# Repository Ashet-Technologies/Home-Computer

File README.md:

# Ashet Home Computer Mk4

### _The 21st century home computer_

| Project Status                                                                                       |
|------------------------------------------------------------------------------------------------------|
| ⚠️ **WORK IN PROGRESS** ⚠️                                                                             |
| This README reflects the state of where the project wants to go, not where the project is right now! |

## Introduction

The Ashet Home Computer bridges the gap between simple microcontroller development boards and modern single-board computers, offering the processing capability to run a full graphical desktop OS while maintaining the hardware accessibility of simpler systems.

Built around the RP2350 dual-core processor, it combines sufficient computational power for a modern user interface with a transparent, education-oriented architecture. The modular expansion system, inspired by classic computer designs, allows direct hardware access while providing proper driver abstractions for portability.

Key differentiators:

- Runs [Ashet OS](https://github.com/Ashet-Technologies/Ashet-OS): A custom desktop operating system with modern GUI capabilities
- Fully documented hardware architecture with direct register access
- Modular expansion through 7 dedicated slots, including specialized video/audio interfaces
- 8 MB RAM and 16 MB Flash supporting both low-level and high-level development
- Comprehensive I/O capabilities suitable for real-time interfacing, creative projects, and systems development

The system is designed for accessibility across different skill levels - from students learning computer architecture to makers building custom hardware interfaces, and from demosceners pushing hardware limits to educators teaching system design.

## Features

The computer follows a modular design similar to a PC where you have expansion cards that you can plug into the system.

### Core Features

These features are available no matter what expansion cards you have installed.

- RP2350 Core
  - Dual-Core System
  - Each Core Might Be
    - Arm CPU (Cortex-M33, 150 MHz)
    - RISC-V CPU (RV32IMAC+, 150 MHz)
- 8 MB RAM
- 16 MB Flash
- USB 1.1 Host
- 10/100 Mbps Ethernet
- Battery-Backed Real-Time Clock
- Status Display (128x64, monochrome)
- Integrated Debug Probe
- 7 Expansion Slots
  - 1 Video Expansion Slot
  - 1 Audio Expansion Slot
  - 5 Generic Expansion Slots

### Standard Expansions

The following expansion cards are the designated expansion cards which make up the Ashet Home Computer as designed:

1. [Framebuffer Video Card](Hardware/Expansions/Framebuffer%20Video/README.md)
    - DVI Video Out (800x480, 60 Hz)
2. [PCM Sound Card](Hardware/Expansions/PCM%20Sound/README.md)
    - PCM Audio Out (48 kHz, 16 bit)
    - PCM Audio In (48 kHz, 16 bit)
3. [USB Card](Hardware/Expansions/USB/README.md)
    - 4 USB 1.1 Host Ports
4. [RS232 Card](Hardware/Expansions/RS232/README.md)
    - TTL UART (3.3V, 5V, ±12V)
5. [Basic I/O Card](Hardware/Expansions/Basic%20IO/README.md)
    - Pin Header Connector
    - 8 GPIOs
    - Dedicated I²C
    - 5 V and 3.3 V power supply available
6. [Commodore Connectivity Card](Hardware/Expansions/Commodore%20Connectivity/README.md)
    - 2× C64 Serial
7. [User Expansion Card](Hardware/Expansions/User%20Expansion/README.md)
    - Minimal Expansion Card
    - Perfboard For Custom Expansions
    - Pin Header Connector

### Other Expansions

There are many more ideas that can be realized with expansion cards.

Take a peek at our [List of Expansion Board Ideas](Concept/Expansion%20Boards.md) or check out the [Expansion Card Interface Specification](Specs/Expansion%20Bus.md) how to create your own.

## Use Cases

This chapter contains a list of things you can do with the computer, ordered loosely by user groups.

### Demosceners

Make a demo, I guess?

With a good audio and video expansion card, and two strong multi-core CPUs the computer packs enough power to create awesome visuals and sound effects.

### Retro-Enthusiasts

The computer is able to emulate a lot of existing machines with fitting I/O connectivity. The backplane is able to emulate a lot of different protocols with cheap passive expansion modules.

It also is able to create a multitude of video signals, analog and digital with 15 or 30 kHz line frequency. Another option is to have more complex expansion cards which can drive storage interfaces like [Shugart bus](https://en.wikipedia.org/wiki/Floppy_disk_drive_interface), [MFM disks](https://en.wikipedia.org/wiki/Modified_frequency_modulation), ATA and IDE…

### Artists / Musicians

The Ashet can be used as a cheap real-time sequencing controller which can handle a good amount of interfaces. With support for MIDI, DMX, analog audio channels and ethernet, it's possible to create complex audio setups. Another option is creating or using expansion cards that provide access to old-school synthesizers like the [AY-3-8910](https://en.wikipedia.org/wiki/General_Instrument_AY-3-8910) or the [SID](https://en.wikipedia.org/wiki/MOS_Technology_6581).

### Hackers / Makers

With the Propeller 2 on the backplane, one can basically emulate any digital interface like SPI or I²C. With a breakout I/O expansion card, it can be used for controlling your own hardware, accessing and changing SPI flashes, ...

It is also possible to use the Ashet as a basic logic analyzer and scope, as well as a signal and waveform generator. With a bigger I/O card, it can be expanded to 32 synchronously processed channels.

By utilizing a scripting language on Ashet OS, one should be able to easily access and bootstrap newly acquired hardware.

### Educators

The project provides extensive documentation, from decision making over the schematic up to the software architecture, so it can be used as an example on how to design a complete computer system.

The machine also looks more like a "real computer" than a Raspberry Pi or other modern single-board computers, so it is more tangible for persons that do not have experience with electronics and might give an easier start.

### Students

The computer provides a good hands-on experience and allows both creating or understanding hardware and software designs and how they play together. The system is also easily expansible and thus allows creating custom hardware modules. The available documentation allows learning basically everything about the computer that is possible to know.

## Comparison with Similar Projects

The following table shows a comparison to other "small" computers. It should help you get an idea where the Ashet Home Computer is in relation to other projects.

| Feature                      | Ashet                                                              | [Raspberry Pi 4](https://www.raspberrypi.com/products/raspberry-pi-4-model-b/specifications/)   | [Arduino Uno REV3](https://store.arduino.cc/products/arduino-uno-rev3) | [Neotron Pico](https://github.com/neotron-Compute/neotron-Pico)                                                                   | [Cody Computer](https://www.codycomputer.org/)          |
|------------------------------|--------------------------------------------------------------------|-------------------------------------------------------------------------------------------------|------------------------------------------------------------------------|-----------------------------------------------------------------------------------------------------------------------------------|---------------------------------------------------------|
| CPU Architecture             | Arm Cortex-M33 (32 bit)                                            | Arm Cortex-A72 (64 bit)                                                                         | ATmega328p (8 bit)                                                     | Arm Cortex-M0+ (32 bit)                                                                                                           | 6502                                                    |
| CPU Model                    | [Rapsberry Pi RP2350](https://www.raspberrypi.com/products/rp2350/) | [Broadcom BCM2711](https://www.raspberrypi.com/documentation/computers/processors.html#bcm2711) | [ATmega328P](https://www.microchip.com/en-us/product/atmega328p)       | [Rapsberry Pi RP2040](https://www.raspberrypi.com/products/rp2040/)                                                               | [W65C02S](https://wdc65xx.com/integrated-circuit)       |
| CPU Cores                    | 2                                                                  | 4                                                                                               | 1                                                                      | 2                                                                                                                                 | 1                                                       |
| CPU Clock                    | 150 MHz                                                            | 1.8 GHz                                                                                         | 16 MHz                                                                 | 133 MHz                                                                                                                           | 1 MHz                                                   |
| System Memory                | 8 MB                                                               | 1, 2, 4 or 8 GB                                                                                 | 2 KB                                                                   | 264 kB                                                                                                                            | 64 kB                                                   |
| Understandable               | ✅                                                                  | ❌                                                                                               | ✅                                                                      | ✅                                                                                                                                 | ✅                                                       |
| Modern I/O                   | ✅                                                                  | ✅                                                                                               | ❌                                                                      | ❌¹                                                                                                                                | ❌                                                       |
| Modular Design               | ✅                                                                  | ❌                                                                                               | ❌                                                                      | ✅                                                                                                                                 | ✅²                                                      |
| Full Documentation Available | ✅                                                                  | ❌                                                                                               | ✅                                                                      | ✅                                                                                                                                 | ✅                                                       |
| Ethernet                     | ✅                                                                  | ✅                                                                                               | ❌                                                                      | ❌                                                                                                                                 | ❌                                                       |
| Parallax Propeller I/O Chip  | ✅ ([Propeller 2](https://www.parallax.com/propeller-2))            | ❌                                                                                               | ❌                                                                      | ❌                                                                                                                                 | ✅ ([Propeller 1](https://www.parallax.com/propeller-1)) |

¹Neotron Pico uses PS/2 for mouse/keyboard and VGA for video.

²Cody Computer has a single cartridge that can be added.

## Architecture

### Block Diagram

## Glossary

<dl>
  <dt>Mainboard</dt>
  <dd>The Mainboard houses the cpu core and everything necessary to run the system, even without <em>Expansion Boards</em> or the <em>Backplane</em>.</dd>

  <dt>Backplane</dt>
  <dd>The Backplane is the interconnect between the <em>Mainboard</em> and <em>Expansion Boards</em>. This board also contains the <em>I/O Southbridge</em></dd>

  <dt>Expansion Board</dt>
  <dd>Expansion Boards provide more capabilities to the computer. They usually add more I/O features, but could also house any other kind of electronics that want to interface with the <em>Mainboard</em>.</dd>

  <dt>Video Expansion Board</dt>
  <dd>A Video Expansion Board is a special expansion that is only installable in a single socket of the <em>Backplane</em>. In addition to the generic <em>Expansion Board</em> interface, it has an additional 8 lanes of high-speed interconnect to the <em>Mainboard</em>.</dd>

  <dt>Audio Expansion</dt>
  <dd>An Audio Expansion Board is a special expansion that is only installable in a single socket of the <em>Backplane</em>. In addition to the generic <em>Expansion Board</em> interface, it has an additional 2-lane I²S interconnect to the <em>Mainboard</em>.</dd>

  <dt>I/O Southbridge</dt>
  <dd>The I/O Southbridge provides the main interconnect between the <em>Main Board</em> and the <em>Expansion Boards</em>. It is realized by a <a href="https://www.parallax.com/propeller-2/">Propeller 2</a>.</dd>
</dl>

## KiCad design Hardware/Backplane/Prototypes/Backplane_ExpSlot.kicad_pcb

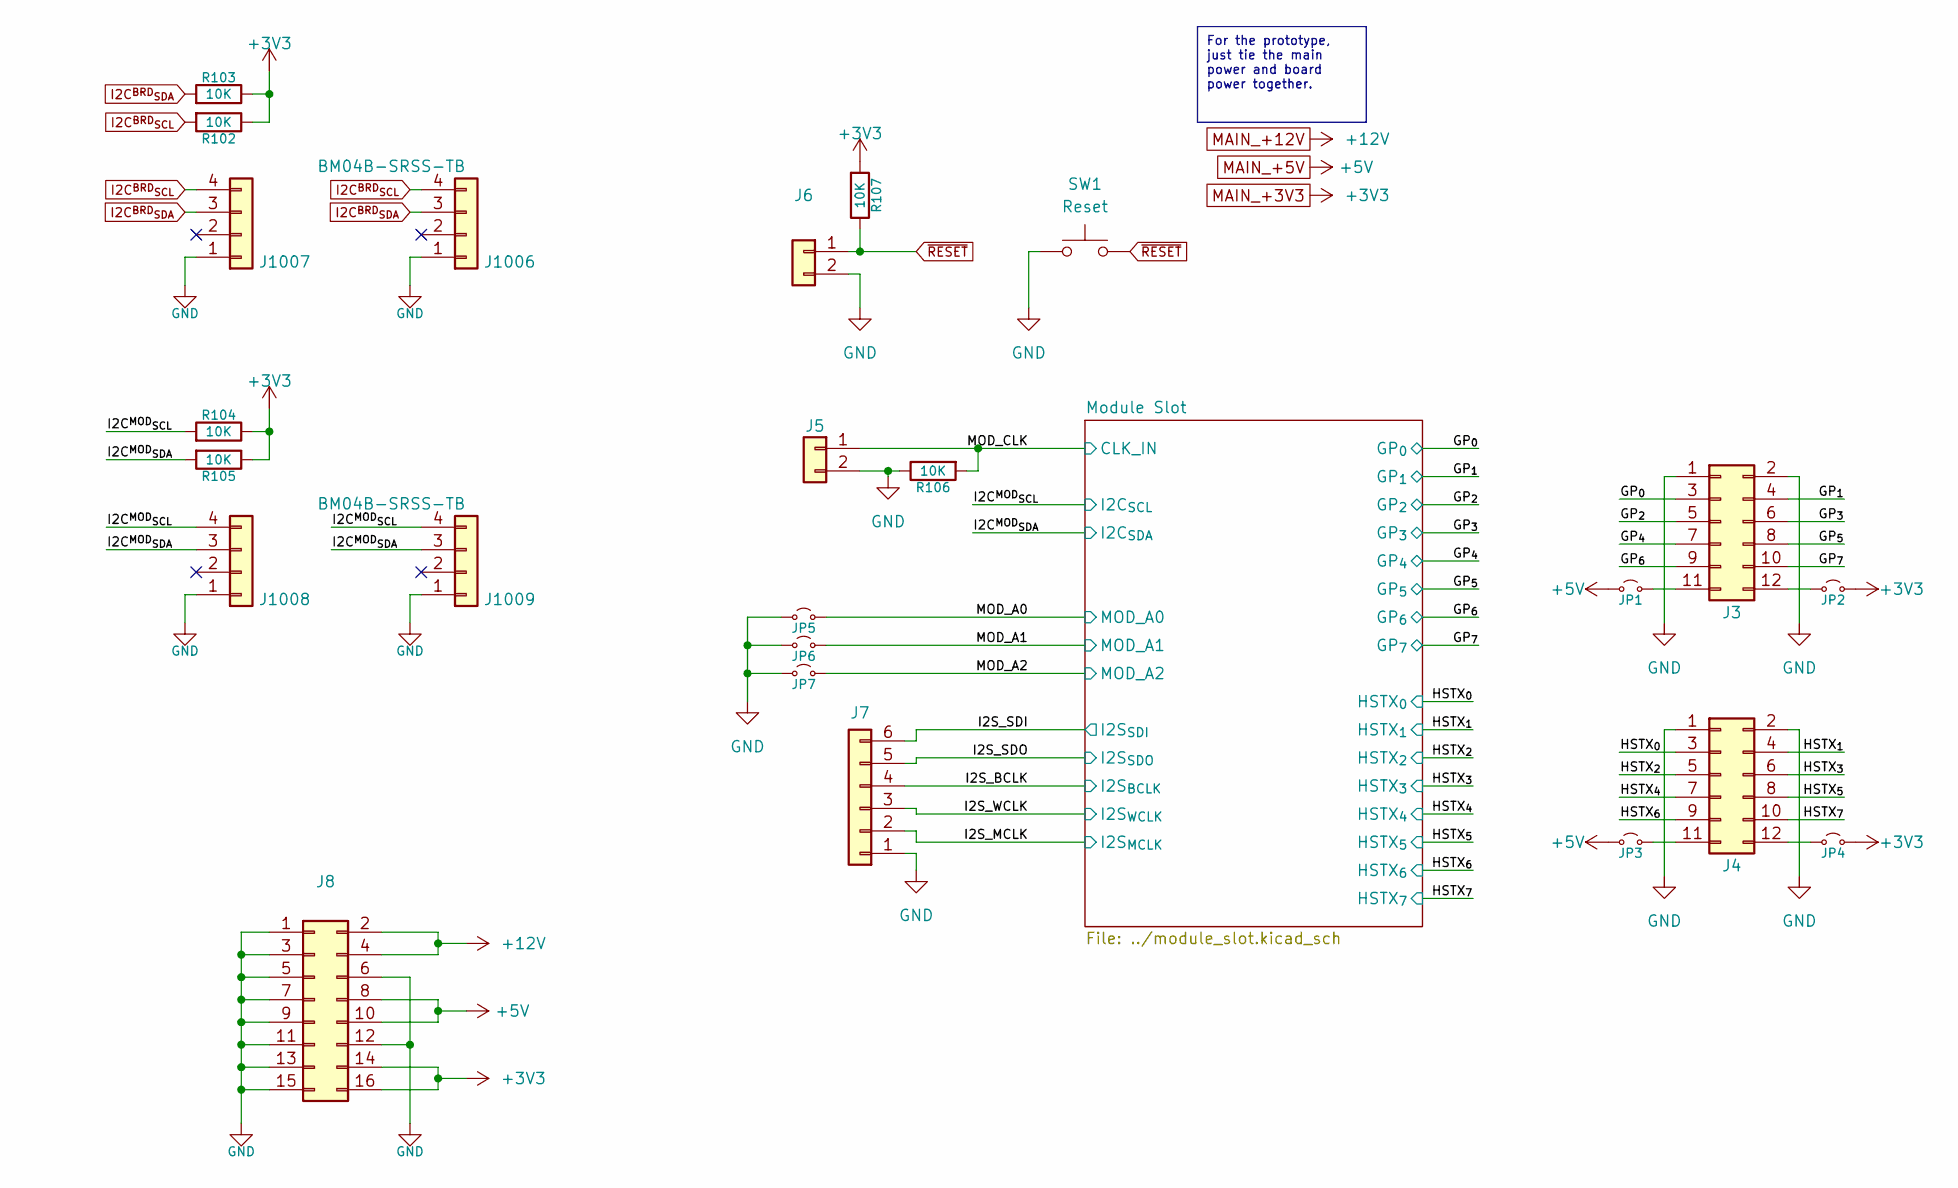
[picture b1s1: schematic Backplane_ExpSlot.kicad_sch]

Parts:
J3: GP; PinHeader_2x06_P2.54mm_Vertical
J4: HSTX; PinHeader_2x06_P2.54mm_Vertical
J5, J6: Conn_01x02; PinHeader_1x02_P2.54mm_Vertical
J7: I²S; PinHeader_1x06_P2.54mm_Vertical
J8: Power; PinHeader_2x08_P2.00mm_Vertical
J1006, J1009: BM04B-SRSS-TB; JST_SH_BM04B-SRSS-TB_1x04-1MP_P1.00mm_Vertical; Digikey Part No 455-BM04B-SRSS-TBCT-ND
J1007, J1008: BM04B-SRSS-TB; PinHeader_1x04_P2.54mm_Vertical
JP1, JP3: +5V; PinHeader_1x02_P2.54mm_Vertical
JP2, JP4: +3V3; PinHeader_1x02_P2.54mm_Vertical
JP5: A0; PinHeader_1x02_P2.54mm_Vertical
JP6: A1; PinHeader_1x02_P2.54mm_Vertical
JP7: A2; PinHeader_1x02_P2.54mm_Vertical
R102, R103, R104, R105, R106, R107: 10K; R_0603_1608Metric; Digikey Part No 311-10.0KHRCT-ND
SW1: Reset; SW_PUSH_6mm_H5mm

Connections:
/GP_{0}: J3.3; also elsewhere on the board
/GP_{1}: J3.4; also elsewhere on the board
/GP_{2}: J3.5; also elsewhere on the board
/GP_{3}: J3.6; also elsewhere on the board
/GP_{4}: J3.7; also elsewhere on the board
/GP_{5}: J3.8; also elsewhere on the board
/GP_{6}: J3.9; also elsewhere on the board
/GP_{7}: J3.10; also elsewhere on the board
/HSTX_{0}: J4.3; also elsewhere on the board
/HSTX_{1}: J4.4; also elsewhere on the board
/HSTX_{2}: J4.5; also elsewhere on the board
/HSTX_{3}: J4.6; also elsewhere on the board
/HSTX_{4}: J4.7; also elsewhere on the board
/HSTX_{5}: J4.8; also elsewhere on the board
/HSTX_{6}: J4.9; also elsewhere on the board
/HSTX_{7}: J4.10; also elsewhere on the board
/I2C^{MOD}_{SCL}: J1008.4, J1009.4, R104.2; also elsewhere on the board
/I2C^{MOD}_{SDA}: J1008.3, J1009.3, R105.2; also elsewhere on the board
/I2S_BCLK: J7.4; also elsewhere on the board
/I2S_MCLK: J7.2; also elsewhere on the board
/I2S_SDI: J7.6; also elsewhere on the board
/I2S_SDO: J7.5; also elsewhere on the board
/I2S_WCLK: J7.3; also elsewhere on the board
/MOD_A0: JP5.2 (B); also elsewhere on the board
/MOD_A1: JP6.2 (B); also elsewhere on the board
/MOD_A2: JP7.2 (B); also elsewhere on the board
/MOD_CLK: J5.1, R106.2; also elsewhere on the board
GND: J3.1, J3.2, J4.1, J4.2, J5.2, J6.2, J7.1, J8.1, J8.3, J8.5, J8.6, J8.7, J8.9, J8.11, J8.12, J8.13, J8.15, J1006.1, J1007.1, J1008.1, J1009.1, JP5.1 (A), JP6.1 (A), JP7.1 (A), R106.1, SW1.1; also elsewhere on the board
I2C^{BRD}_{SCL}: J1006.4, J1007.4, R102.2; also elsewhere on the board
I2C^{BRD}_{SDA}: J1006.3, J1007.3, R103.2; also elsewhere on the board
MAIN_+3V3: J8.14, J8.16, JP2.2 (B), JP4.2 (B), R102.1, R103.1, R104.1, R105.1, R107.2; also elsewhere on the board
MAIN_+5V: J8.8, J8.10, JP1.1 (A), JP3.1 (A); also elsewhere on the board
MAIN_+12V: J8.2, J8.4; also elsewhere on the board
unnamed: J3.11, JP1.2 (B)
unnamed: J3.12, JP2.1 (A)
unnamed: J4.11, JP3.2 (B)
unnamed: J4.12, JP4.1 (A)
~RESET: J6.1, R107.1, SW1.2; also elsewhere on the board

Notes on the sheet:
For the prototype, just tie the main power and board power together.

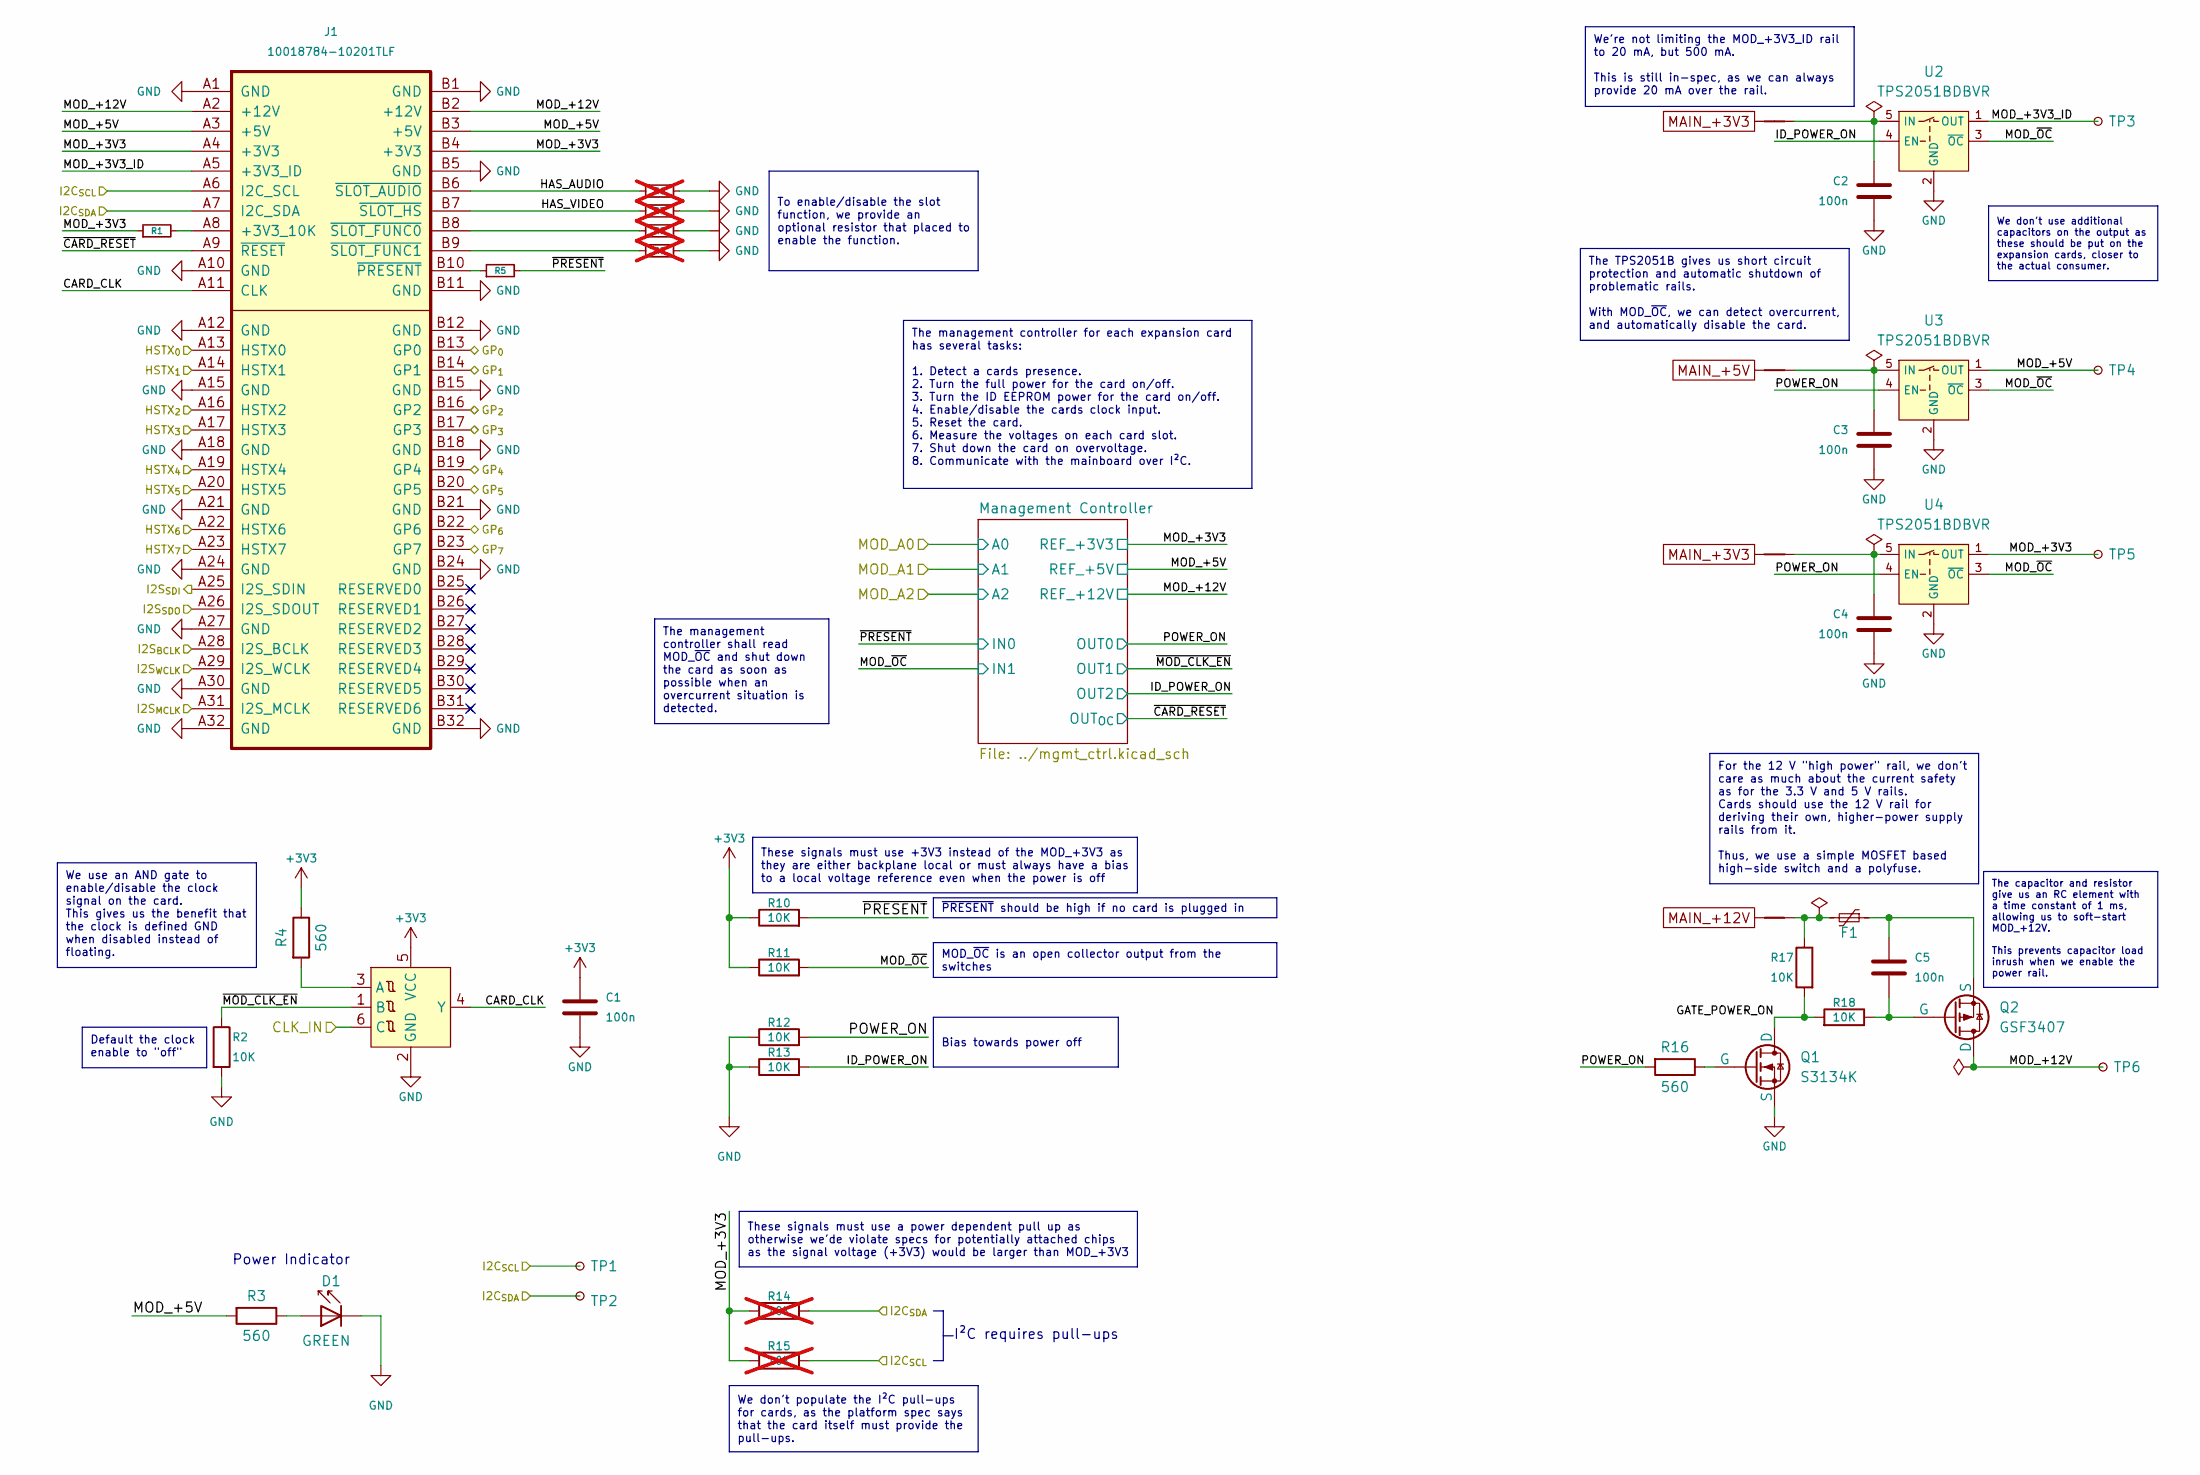
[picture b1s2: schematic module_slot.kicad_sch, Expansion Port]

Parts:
C1, C2, C3, C4, C5: 100n; C_0603_1608Metric; Digikey Part No 399-C0603C104M4RACTUCT-ND
D1: GREEN; LED_0603_1608Metric
F1: SMD1206B050TF/15; Fuse_1206_3216Metric; Digikey Part No 13-SMD1206B050TF/15TR-ND
J1: 10018784-10201TLF; CONN_10018784-10201TLF; Digikey Part No 609-2026-ND
NT1, NT2, NT3, NT4: NetTie_2; NetTie-2_SMD_Pad0.5mm
Q1: S3134K; SOT-23; Digikey Part No 4786-S3134KCT-ND
Q2: GSF3407; SOT-23; Digikey Part No 4786-GSF3407CT-ND
R1, R2, R10, R11, R12, R13, R17, R18: 10K; R_0603_1608Metric; Digikey Part No 311-10.0KHRCT-ND
R3, R4, R16: 560; R_0603_1608Metric; Digikey Part No RR08P560DCT-ND
R5: 0; R_0603_1608Metric; Digikey Part No 311-0.0GRCT-ND
R6, R7, R8, R9: 0; R_0603_1608Metric; Digikey Part No 311-0.0GRCT-ND; not fitted
R14, R15: 10K; R_0603_1608Metric; Digikey Part No 311-10.0KHRCT-ND; not fitted
TP1, TP2, TP3, TP4, TP5, TP6: TestPoint_Small; TestPoint_Pad_D1.0mm
U1: NL7SZ57DBVT1G; SC-74-6_1.55x2.9mm_P0.95mm; DigiKey Part No. 488-NL7SZ57DBVT1GCT-ND
U2, U3, U4: TPS2051BDBVR; SOT-23-5; DigiKey Part No. 296-21265-1-ND

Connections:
/GP_{0}: J1.B13 (GP0); also elsewhere on the board
/GP_{1}: J1.B14 (GP1); also elsewhere on the board
/GP_{2}: J1.B16 (GP2); also elsewhere on the board
/GP_{3}: J1.B17 (GP3); also elsewhere on the board
/GP_{4}: J1.B19 (GP4); also elsewhere on the board
/GP_{5}: J1.B20 (GP5); also elsewhere on the board
/GP_{6}: J1.B22 (GP6); also elsewhere on the board
/GP_{7}: J1.B23 (GP7); also elsewhere on the board
/HSTX_{0}: J1.A13 (HSTX0); also elsewhere on the board
/HSTX_{1}: J1.A14 (HSTX1); also elsewhere on the board
/HSTX_{2}: J1.A16 (HSTX2); also elsewhere on the board
/HSTX_{3}: J1.A17 (HSTX3); also elsewhere on the board
/HSTX_{4}: J1.A19 (HSTX4); also elsewhere on the board
/HSTX_{5}: J1.A20 (HSTX5); also elsewhere on the board
/HSTX_{6}: J1.A22 (HSTX6); also elsewhere on the board
/HSTX_{7}: J1.A23 (HSTX7); also elsewhere on the board
/I2C^{MOD}_{SCL}: J1.A6 (I2C_SCL), R15.2, TP1.1 (1_1); also elsewhere on the board
/I2C^{MOD}_{SDA}: J1.A7 (I2C_SDA), R14.2, TP2.1 (1_1); also elsewhere on the board
/I2S_BCLK: J1.A28 (I2S_BCLK); also elsewhere on the board
/I2S_MCLK: J1.A31 (I2S_MCLK); also elsewhere on the board
/I2S_SDI: J1.A25 (I2S_SDIN); also elsewhere on the board
/I2S_SDO: J1.A26 (I2S_SDOUT); also elsewhere on the board
/I2S_WCLK: J1.A29 (I2S_WCLK); also elsewhere on the board
/MOD_CLK: U1.6 (C); also elsewhere on the board
/Module Slot/CARD_CLK: J1.A11 (CLK), U1.4 (Y)
/Module Slot/GATE_POWER_ON: Q1.3 (D), R17.2, R18.2
/Module Slot/HAS_AUDIO: J1.B6 (~SLOT_AUDIO), R6.1
/Module Slot/HAS_VIDEO: J1.B7 (~SLOT_HS), R7.1
/Module Slot/ID_POWER_ON: R13.2, U2.4 (EN); also elsewhere on the board
/Module Slot/MOD_+3V3: J1.A4 (+3V3), J1.B4 (+3V3), R1.1, R14.1, R15.1, TP5.1 (1_1), U4.1 (OUT); also elsewhere on the board
/Module Slot/MOD_+3V3_ID: J1.A5 (+3V3_ID), TP3.1 (1_1), U2.1 (OUT)
/Module Slot/MOD_+5V: J1.A3 (+5V), J1.B3 (+5V), R3.2, TP4.1 (1_1), U3.1 (OUT); also elsewhere on the board
/Module Slot/MOD_+12V: J1.A2 (+12V), J1.B2 (+12V), Q2.3 (D), TP6.1 (1_1); also elsewhere on the board
/Module Slot/MOD_~OC: R11.2, U2.3 (~OC), U3.3 (~OC), U4.3 (~OC); also elsewhere on the board
/Module Slot/POWER_ON: R12.2, R16.2, U3.4 (EN), U4.4 (EN); also elsewhere on the board
/Module Slot/~CARD_RESET: J1.A9 (~RESET); also elsewhere on the board
/Module Slot/~MOD_CLK_EN: R2.1, U1.1 (B); also elsewhere on the board
/Module Slot/~PRESENT: R5.2, R10.2; also elsewhere on the board
GND: C1.1, C2.1, C3.1, C4.1, D1.1 (K), J1.A1 (GND), J1.A10 (GND), J1.A12 (GND), J1.A15 (GND), J1.A18 (GND), J1.A21 (GND), J1.A24 (GND), J1.A27 (GND), J1.A30 (GND), J1.A32 (GND), J1.B1 (GND), J1.B5 (GND), J1.B11 (GND), J1.B12 (GND), J1.B15 (GND), J1.B18 (GND), J1.B21 (GND), J1.B24 (GND), J1.B32 (GND), Q1.2 (S), R2.2, R6.2, R7.2, R8.2, R9.2, R12.1, R13.1, U1.2 (GND), U2.2 (GND), U3.2 (GND), U4.2 (GND); also elsewhere on the board
MAIN_+3V3: C1.2, NT1.1, NT3.1, R4.1, R10.1, R11.1, U1.5 (VCC); also elsewhere on the board
MAIN_+5V: NT2.1; also elsewhere on the board
MAIN_+12V: NT4.1; also elsewhere on the board
unnamed: D1.2 (A), R3.1
unnamed: F1.2, NT4.2, R17.1
unnamed: J1.A8 (+3V3_10K), R1.2
unnamed: J1.B10 (~PRESENT), R5.1
unnamed: J1.B8 (~SLOT_FUNC0), R8.1
unnamed: J1.B9 (~SLOT_FUNC1), R9.1
unnamed: Q1.1 (G), R16.1
unnamed: C5.1, Q2.1 (G), R18.1
unnamed: C5.2, F1.1, Q2.2 (S)
unnamed: R4.2, U1.3 (A)
unnamed: C2.2, NT1.2, U2.5 (IN)
unnamed: C3.2, NT2.2, U3.5 (IN)
unnamed: C4.2, NT3.2, U4.5 (IN)

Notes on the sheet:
I²C requires pull-ups
Power Indicator
We use an AND gate to enable/disable the clock signal on the card. This gives us the benefit that the clock is defined GND when disabled instead of floating.
The TPS2051B gives us short circuit protection and automatic shutdown of problematic rails. With MOD_~{OC}, we can detect overcurrent, and automatically disable the card.
The management controller shall read MOD_~{OC} and shut down the card as soon as possible when an overcurrent situation is detected.
These signals must use +3V3 instead of the MOD_+3V3 as they are either backplane local or must always have a bias to a local voltage reference even when the power is off
For the 12 V "high power" rail, we don't care as much about the current safety as for the 3.3 V and 5 V rails. Cards should use the 12 V rail for deriving their own, higher-power supply rails from it. Thus, we use a simple MOSFET based high-side switch and a polyfuse.
Default the clock enable to "off"
Bias towards power off
MOD_~{OC} is an open collector output from the switches
~{PRESENT} should be high if no card is plugged in
The management controller for each expansion card has several tasks: 1. Detect a cards presence. 2. Turn the full power for the card on/off. 3. Turn the ID EEPROM power for the card on/off. 4. Enable/disable the cards clock input. 5. Reset the card. 6. Measure the voltages on each card slot. 7. Shu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
These signals must use a power dependent pull up as otherwise we'de violate specs for potentially attached chips as the signal voltage (+3V3) would be larger than MOD_+3V3
We don't populate the I²C pull-ups for cards, as the platform spec says that the card itself must provide the pull-ups.
We don't use additional capacitors on the output as these should be put on the expansion cards, closer to the actual consumer.
To enable/disable the slot function, we provide an optional resistor that placed to enable the function.
The capacitor and resistor give us an RC element with a time constant of 1 ms, allowing us to soft-start MOD_+12V. This prevents capacitor load inrush when we enable the power rail.
We're not limiting the MOD_+3V3_ID rail to 20 mA, but 500 mA. This is still in-spec, as we can always provide 20 mA over the rail.

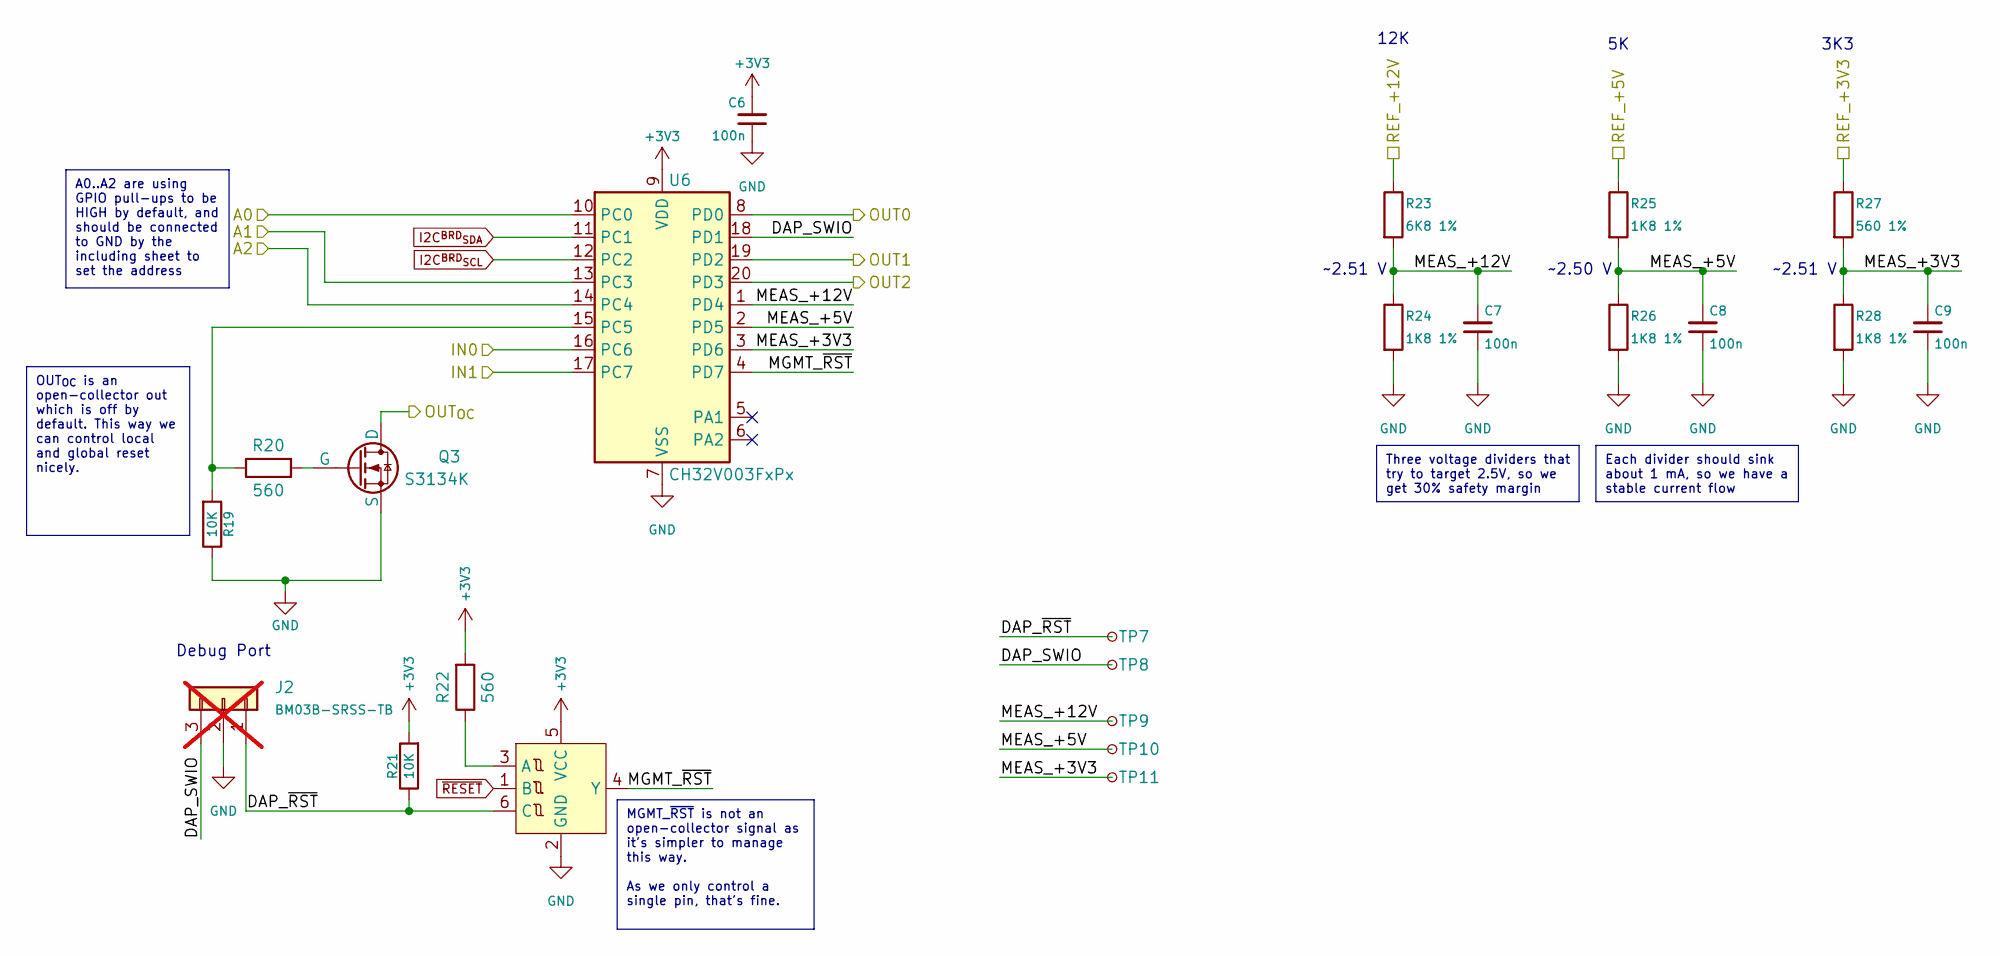
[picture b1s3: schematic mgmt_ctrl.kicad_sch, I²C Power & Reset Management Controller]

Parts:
C6, C7, C8, C9: 100n; C_0603_1608Metric; Digikey Part No 399-C0603C104M4RACTUCT-ND
J2: BM03B-SRSS-TB; JST_SH_BM03B-SRSS-TB_1x03-1MP_P1.00mm_Vertical; Digikey Part No 455-BM03B-SRSS-TBTR-ND; not fitted
Q3: S3134K; SOT-23; Digikey Part No 4786-S3134KCT-ND
R19, R21: 10K; R_0603_1608Metric; Digikey Part No 311-10.0KHRCT-ND
R20, R22: 560; R_0603_1608Metric; Digikey Part No RR08P560DCT-ND
R23: 6K8 1%; R_0603_1608Metric; Digikey Part No RG16P6.8KBCT-ND
R24, R25, R26, R28: 1K8 1%; R_0603_1608Metric; Digikey Part No RG16P1.8KBCT-ND
R27: 560 1%; R_0603_1608Metric; Digikey Part No RR08P560DCT-ND
TP7, TP8, TP9, TP10, TP11: TestPoint_Small; TestPoint_Pad_D1.0mm
U5: NL7SZ57DBVT1G; SC-74-6_1.55x2.9mm_P0.95mm; DigiKey Part No. 488-NL7SZ57DBVT1GCT-ND
U6: CH32V003FxPx; TSSOP-20_4.4x6.5mm_P0.65mm; Digikey Part No 1188-SMDICCH32V003F4P6-ND

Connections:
/MOD_A0: U6.10 (PC0); also elsewhere on the board
/MOD_A1: U6.13 (PC3); also elsewhere on the board
/MOD_A2: U6.14 (PC4); also elsewhere on the board
/Module Slot/ID_POWER_ON: U6.20 (PD3); also elsewhere on the board
/Module Slot/MOD_+3V3: R27.1; also elsewhere on the board
/Module Slot/MOD_+5V: R25.1; also elsewhere on the board
/Module Slot/MOD_+12V: R23.1; also elsewhere on the board
/Module Slot/MOD_~OC: U6.17 (PC7); also elsewhere on the board
/Module Slot/Management Controller/DAP_SWIO: J2.3, TP8.1 (1_1), U6.18 (PD1)
/Module Slot/Management Controller/DAP_~RST: J2.1, R21.1, TP7.1 (1_1), U5.6 (C)
/Module Slot/Management Controller/MEAS_+3V3: C9.2, R27.2, R28.1, TP11.1 (1_1), U6.3 (PD6)
/Module Slot/Management Controller/MEAS_+5V: C8.2, R25.2, R26.1, TP10.1 (1_1), U6.2 (PD5)
/Module Slot/Management Controller/MEAS_+12V: C7.2, R23.2, R24.1, TP9.1 (1_1), U6.1 (PD4)
/Module Slot/Management Controller/MGMT_~RST: U5.4 (Y), U6.4 (PD7)
/Module Slot/POWER_ON: U6.8 (PD0); also elsewhere on the board
/Module Slot/~CARD_RESET: Q3.3 (D); also elsewhere on the board
/Module Slot/~MOD_CLK_EN: U6.19 (PD2); also elsewhere on the board
/Module Slot/~PRESENT: U6.16 (PC6); also elsewhere on the board
GND: C6.1, C7.1, C8.1, C9.1, J2.2, Q3.2 (S), R19.1, R24.2, R26.2, R28.2, U5.2 (GND), U6.7 (VSS); also elsewhere on the board
I2C^{BRD}_{SCL}: U6.12 (PC2); also elsewhere on the board
I2C^{BRD}_{SDA}: U6.11 (PC1); also elsewhere on the board
MAIN_+3V3: C6.2, R21.2, R22.2, U5.5 (VCC), U6.9 (VDD); also elsewhere on the board
unnamed: Q3.1 (G), R20.2
unnamed: R22.1, U5.3 (A)
unnamed: R19.2, R20.1, U6.15 (PC5)
~RESET: U5.1 (B); also elsewhere on the board

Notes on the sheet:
~2.51 V
3K3
Debug Port
12K
~2.50 V
MGMT_~{RST} is not an open-collector signal as it's simpler to manage this way. As we only control a single pin, that's fine.
Each divider should sink about 1 mA, so we have a stable current flow
Three voltage dividers that try to target 2.5V, so we get 30% safety margin
OUT_{OC} is an open-collector out which is off by default. This way we can control local and global reset nicely.
A0..A2 are using GPIO pull-ups to be HIGH by default, and should be connected to GND by the including sheet to set the address

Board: 2 copper layers, 89 parts (0 on the bottom side), 74 nets, no tracks yet.
